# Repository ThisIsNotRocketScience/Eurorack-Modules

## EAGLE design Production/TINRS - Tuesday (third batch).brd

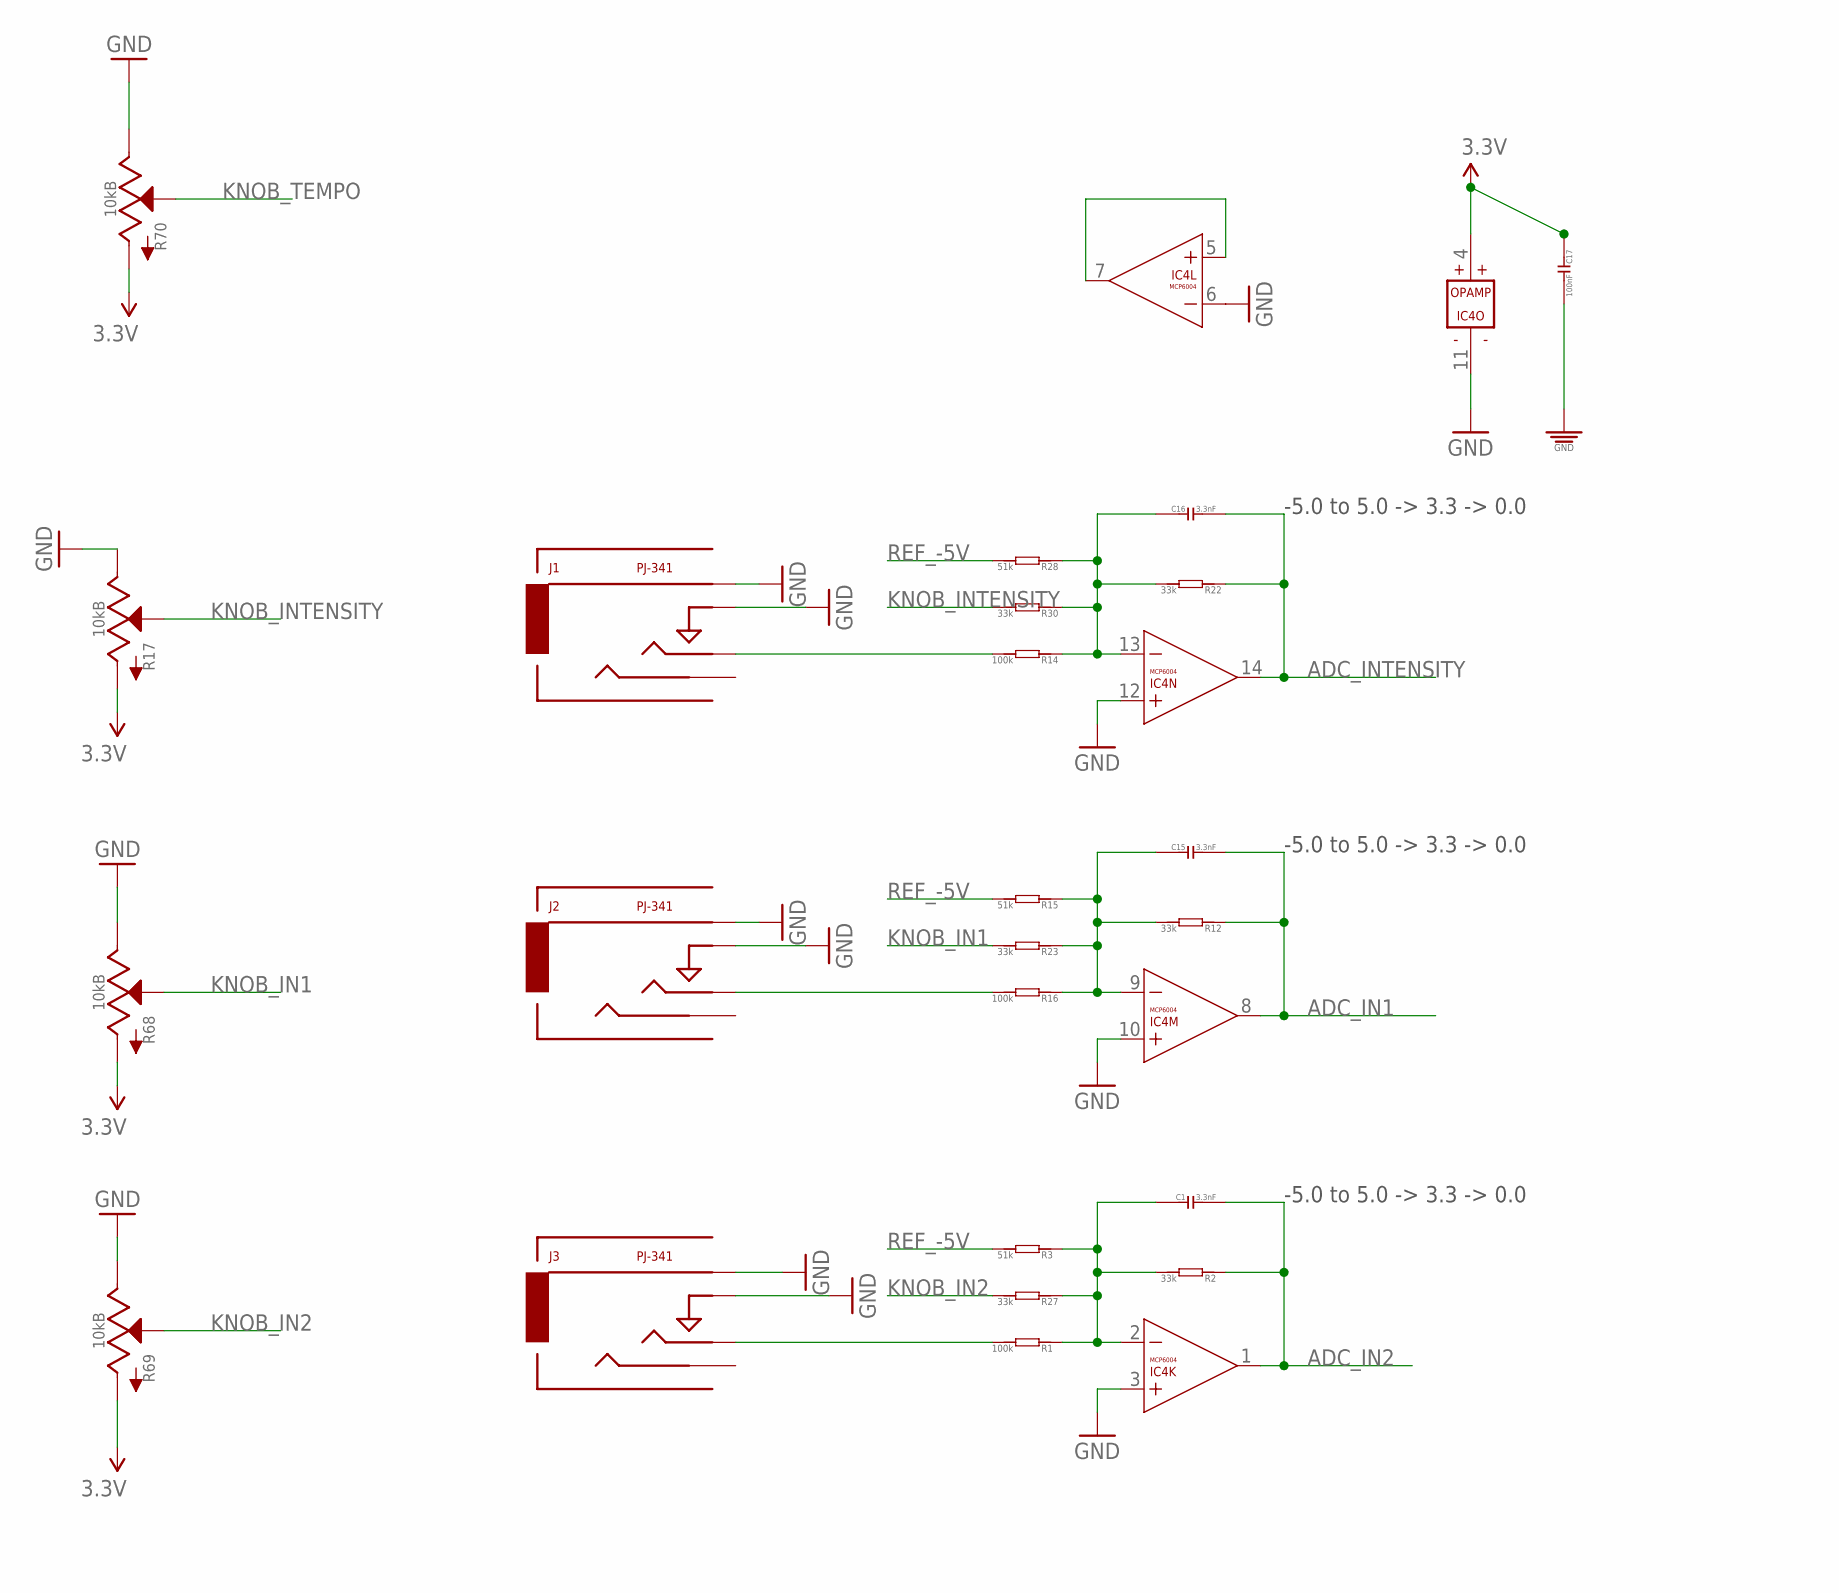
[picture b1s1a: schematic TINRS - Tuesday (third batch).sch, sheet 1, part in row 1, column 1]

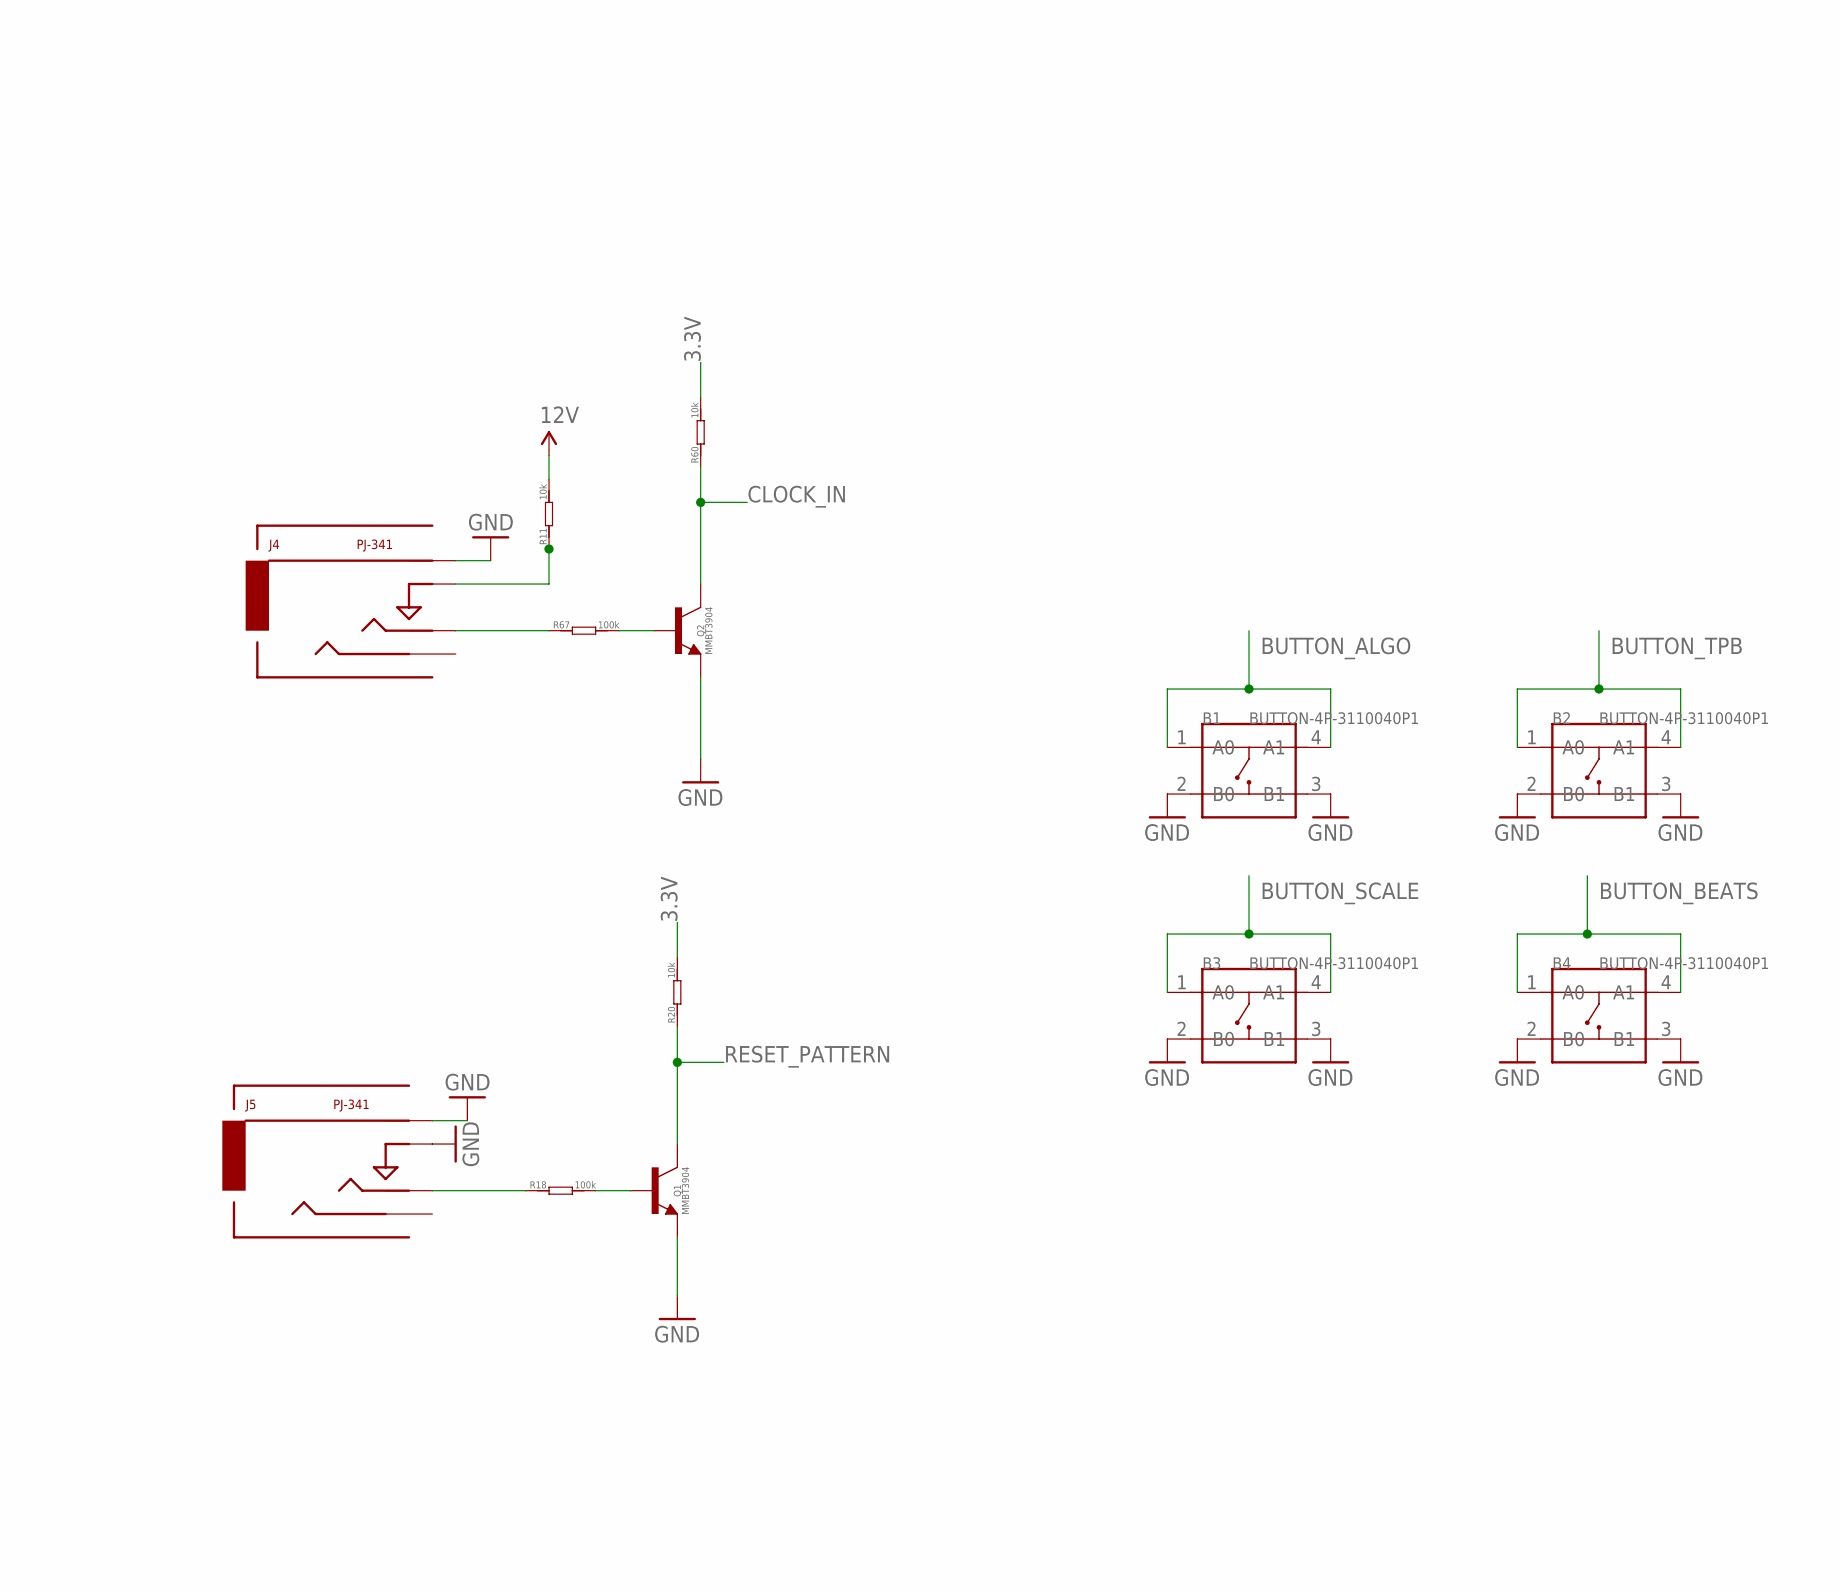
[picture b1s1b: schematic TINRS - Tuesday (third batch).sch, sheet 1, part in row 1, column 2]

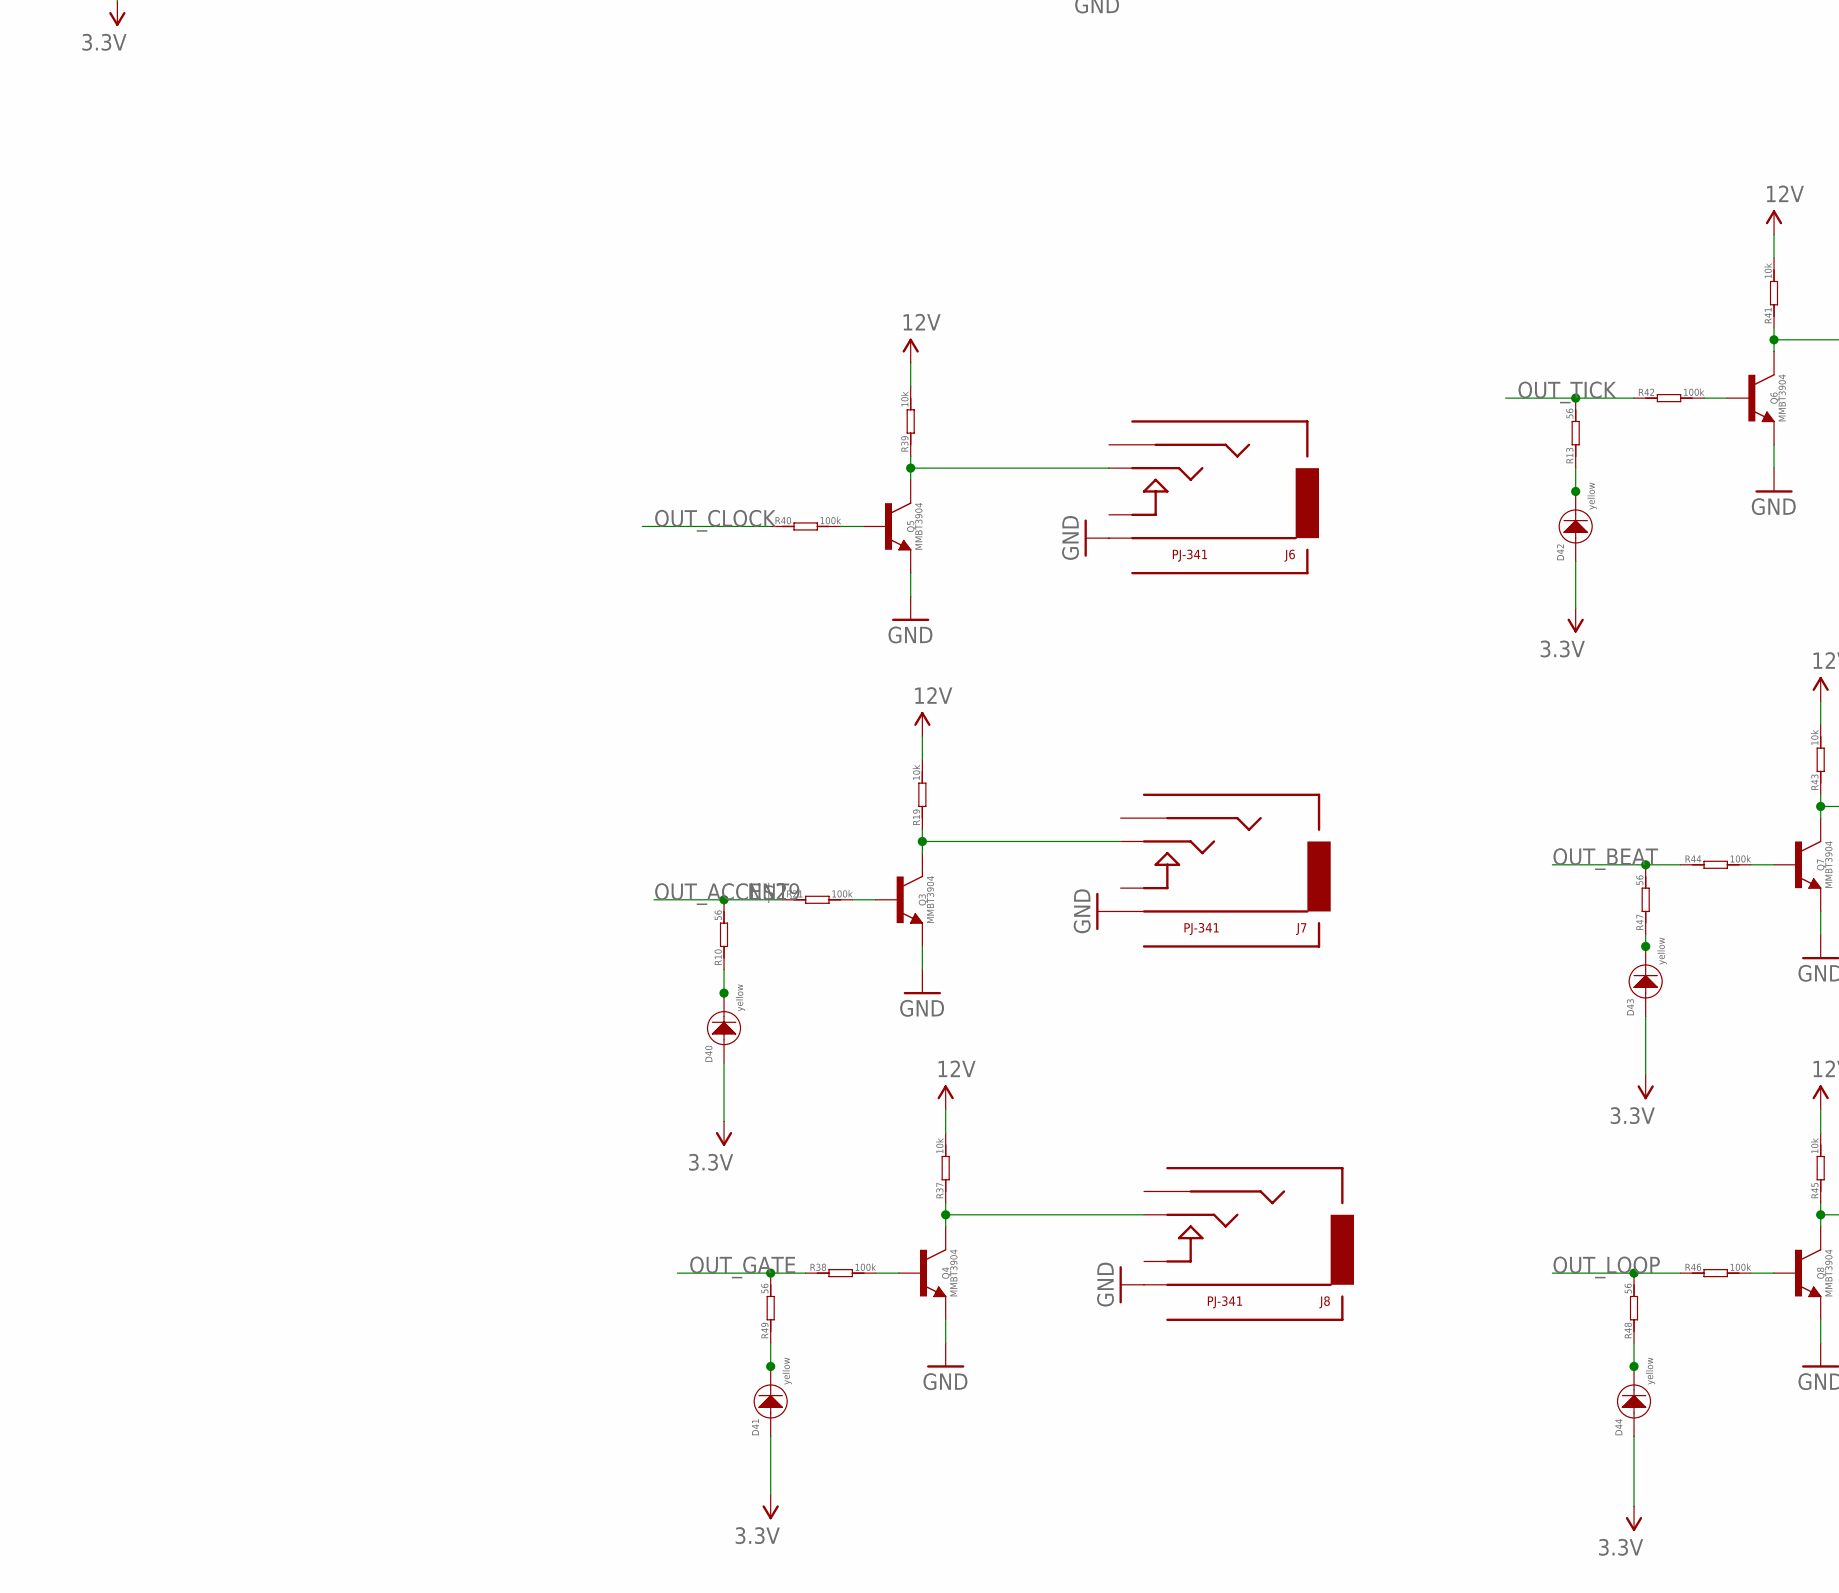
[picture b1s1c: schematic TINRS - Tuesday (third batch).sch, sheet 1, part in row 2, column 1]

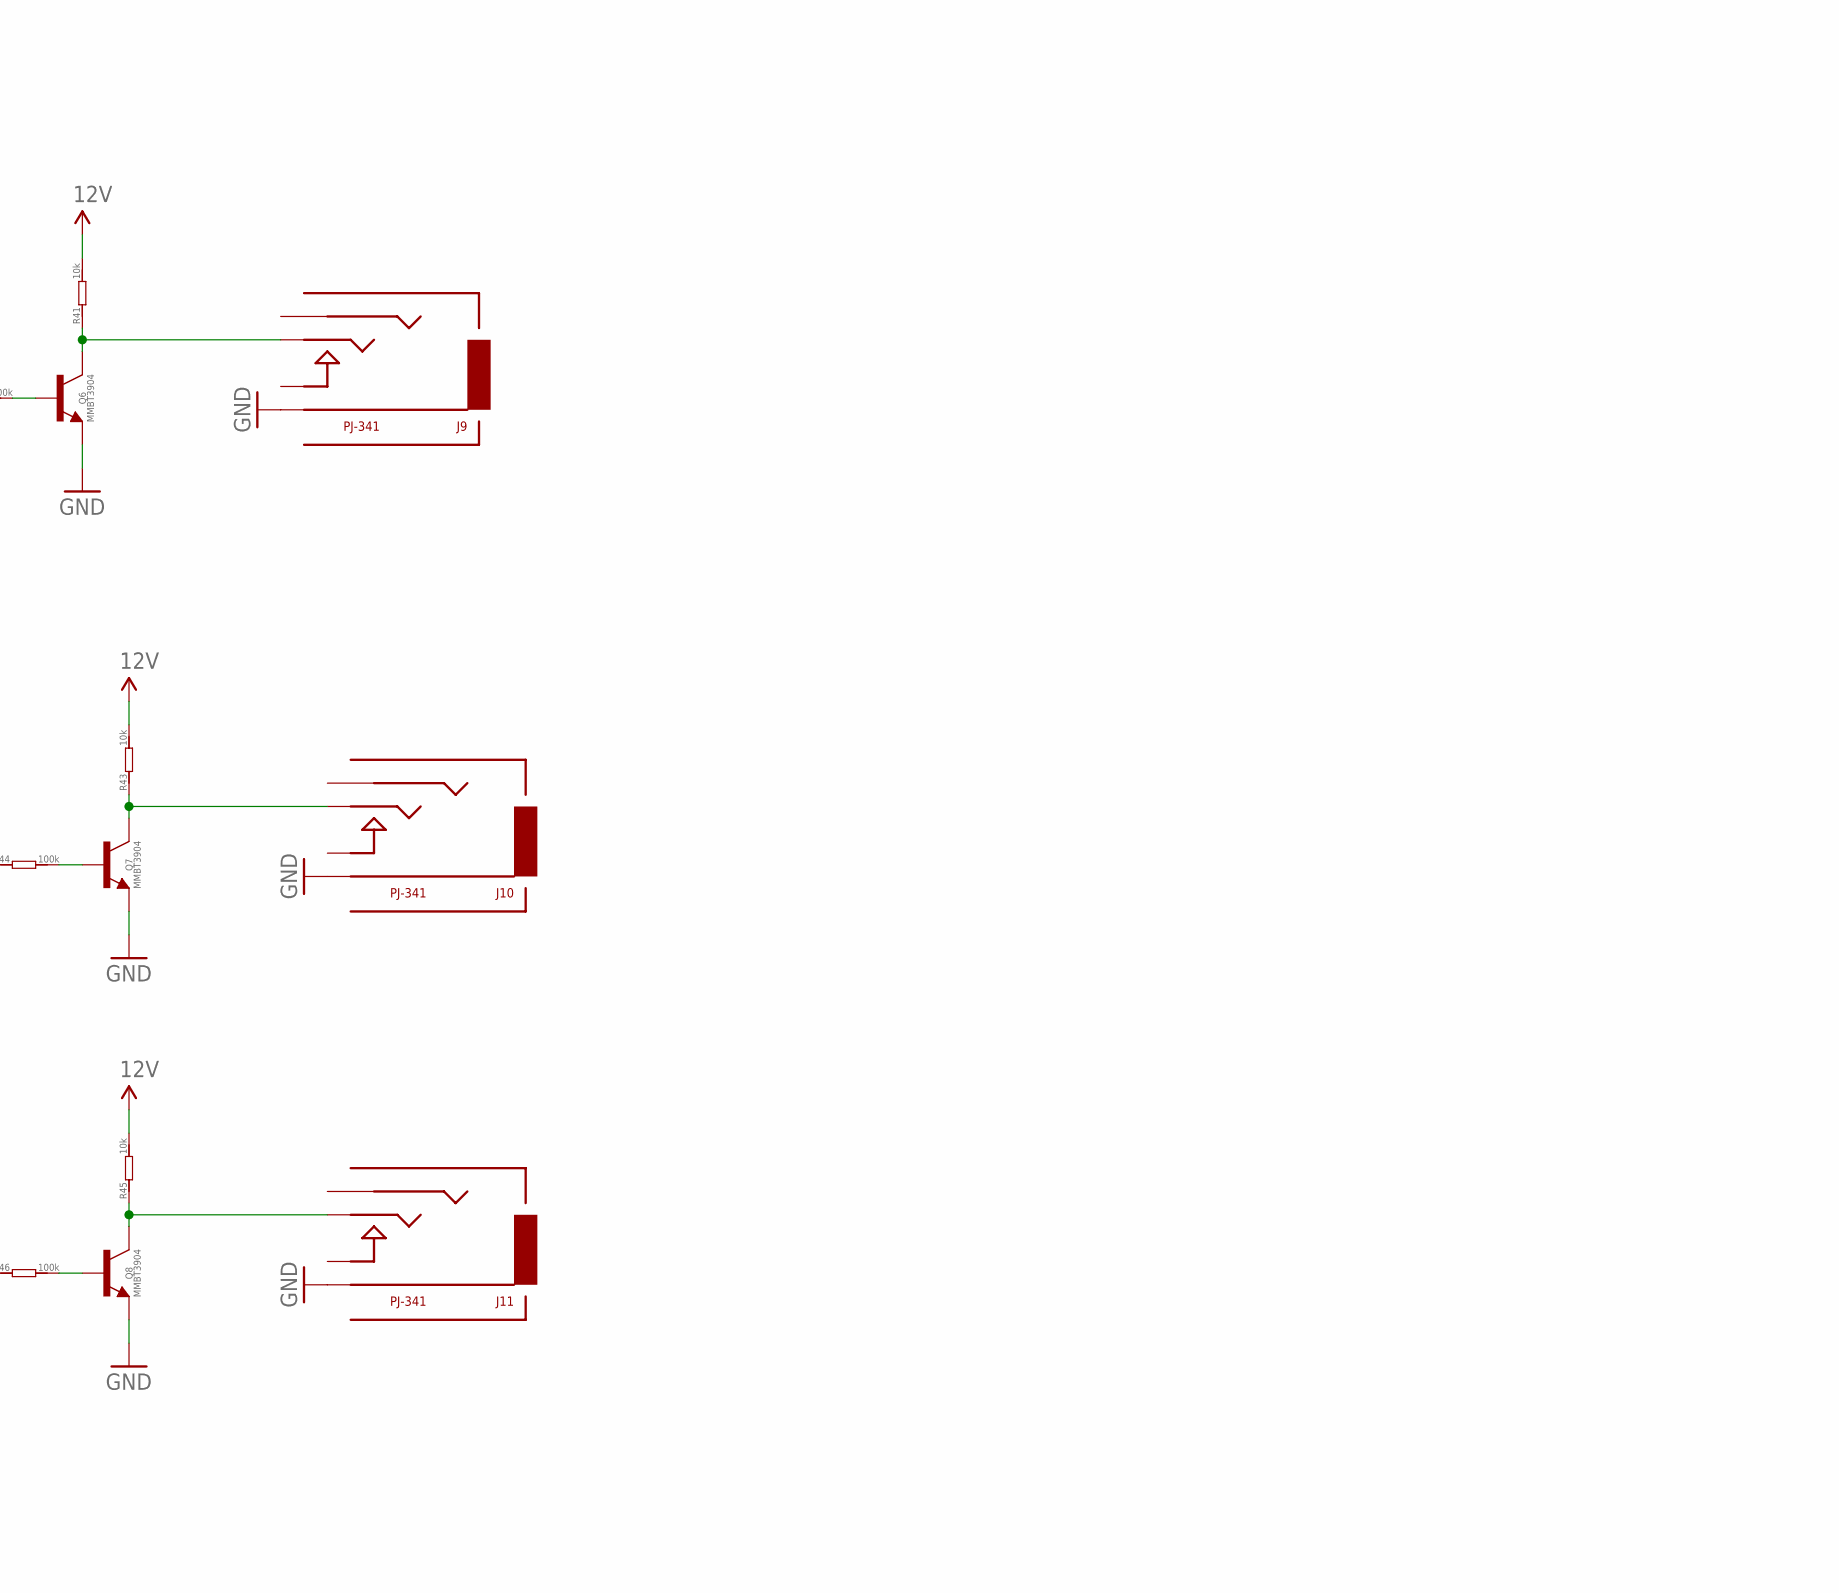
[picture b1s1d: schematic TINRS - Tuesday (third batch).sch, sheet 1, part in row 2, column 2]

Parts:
B1, B2, B3, B4: BUTTON-4P-3110040P1; 4P-6.0X6.0X5.0H
C1, C15, C16: 3.3nF; C0603
C17: 100nF; C0603; MPN MC0603F104Z160CT
D40, D41, D42, D43, D44: yellow; 3MMLED
IC4: MCP6004; SO14; MPN MCP6004-I/SL.
J1, J2, J3, J4, J5: PJ-341; 3.5MM-JACK-SWITCH-13MM-INPUT
J6, J7, J8, J9, J10, J11: PJ-341; 3.5MM-JACK-SWITCH-13MM-OUTPUT
Q1, Q2, Q3, Q4, Q5, Q6, Q7, Q8: MMBT3904; SOT23-BEC; MPN PMBT3904,215
R1, R14, R16, R18, R21, R38, R40, R42, R44, R46, R67: 100k; R0603
R2, R12, R22, R23, R27, R30: 33k; R0603
R3, R15, R28: 51k; R0603
R10, R13, R47, R48, R49: 56; R0603
R11, R19, R20, R37, R39, R41, R43, R45, R60: 10k; R0603
R17, R68, R69, R70: 10kB; ALPS_POT_SQUAREHOLES

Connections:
3.3V: C17.1, D40.+, D41.+, D42.+, D43.+, D44.+, IC4.4 (V+), R17.P$3 (A), R20.2, R60.2, R68.P$3 (A), R69.P$3 (A), R70.P$3 (A); also elsewhere on the board
12V: R11.2, R19.2, R37.2, R39.2, R41.2, R43.2, R45.2; also elsewhere on the board
ADC_IN1: C15.2, IC4.8 (OUT), R12.1; also elsewhere on the board
ADC_IN2: C1.2, IC4.1 (OUT), R2.1; also elsewhere on the board
ADC_INTENSITY: C16.2, IC4.14 (OUT), R22.1; also elsewhere on the board
BUTTON_ALGO: B1.1 (A0), B1.4 (A1); also elsewhere on the board
BUTTON_BEATS: B4.1 (A0), B4.4 (A1); also elsewhere on the board
BUTTON_SCALE: B3.1 (A0), B3.4 (A1); also elsewhere on the board
BUTTON_TPB: B2.1 (A0), B2.4 (A1); also elsewhere on the board
CLOCK_IN: Q2.C, R60.1; also elsewhere on the board
D21: D43.-, R47.1
GND: B1.2 (B0), B1.3 (B1), B2.2 (B0), B2.3 (B1), B3.2 (B0), B3.3 (B1), B4.2 (B0), B4.3 (B1), C17.2, IC4.3 (+IN), IC4.6 (-IN), IC4.10 (+IN), IC4.11 (V-), IC4.12 (+IN), J1.RING@3 (RING), J1.SWITCH@3 (SWITCH), J2.RING@3 (RING), J2.SWITCH@3 (SWITCH), J3.RING@3 (RING), J3.SWITCH@3 (SWITCH), J4.RING@3 (RING), J5.RING@3 (RING), J5.SWITCH@3 (SWITCH), J6.RING@3 (RING), J7.RING@3 (RING), J8.RING@3 (RING), J9.RING@3 (RING), J10.RING@3 (RING), J11.RING@3 (RING), Q1.E, Q2.E, Q3.E, Q4.E, Q5.E, Q6.E, Q7.E, Q8.E, R17.P$1 (E), R68.P$1 (E), R69.P$1 (E), R70.P$1 (E); also elsewhere on the board
KNOB_IN1: R23.2, R68.P$2 (S)
KNOB_IN2: R27.2, R69.P$2 (S)
KNOB_INTENSITY: R17.P$2 (S), R30.2
KNOB_TEMPO: R70.P$2 (S); also elsewhere on the board
unnamed: J2.TIP@3 (TIP), R16.2
unnamed: C15.1, IC4.9 (-IN), R12.2, R15.1, R16.1, R23.1
unnamed: J3.TIP@3 (TIP), R1.2
unnamed: C1.1, IC4.2 (-IN), R1.1, R2.2, R3.1, R27.1
unnamed: D42.-, R13.1
unnamed: Q1.B, R18.2
unnamed: J5.TIP@3 (TIP), R18.1
unnamed: D40.-, R10.1
unnamed: Q3.B, R21.2
unnamed: J7.TIP@3 (TIP), Q3.C, R19.1
unnamed: J1.TIP@3 (TIP), R14.2
unnamed: C16.1, IC4.13 (-IN), R14.1, R22.2, R28.1, R30.1
unnamed: J4.TIP@3 (TIP), R67.1
unnamed: D41.-, R49.1
unnamed: D44.-, R48.1
unnamed: Q4.B, R38.2
unnamed: J8.TIP@3 (TIP), Q4.C, R37.1
unnamed: Q5.B, R40.2
unnamed: J6.TIP@3 (TIP), Q5.C, R39.1
unnamed: Q6.B, R42.2
unnamed: J9.TIP@3 (TIP), Q6.C, R41.1
unnamed: Q2.B, R67.2
unnamed: Q7.B, R44.2
unnamed: J10.TIP@3 (TIP), Q7.C, R43.1
unnamed: Q8.B, R46.2
unnamed: J11.TIP@3 (TIP), Q8.C, R45.1
unnamed: J4.SWITCH@3 (SWITCH), R11.1
unnamed: IC4.5 (+IN), IC4.7 (OUT)
OUT_ACCENT: R10.2, R21.1; also elsewhere on the board
OUT_BEAT: R44.1, R47.2; also elsewhere on the board
OUT_CLOCK: R40.1; also elsewhere on the board
OUT_GATE: R38.1, R49.2; also elsewhere on the board
OUT_LOOP: R46.1, R48.2; also elsewhere on the board
OUT_TICK: R13.2, R42.1; also elsewhere on the board
REF_-5V: R3.2, R15.2, R28.2; also elsewhere on the board
RESET_PATTERN: Q1.C, R20.1; also elsewhere on the board

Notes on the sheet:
-5.0 to 5.0 -> 3.3 -> 0.0

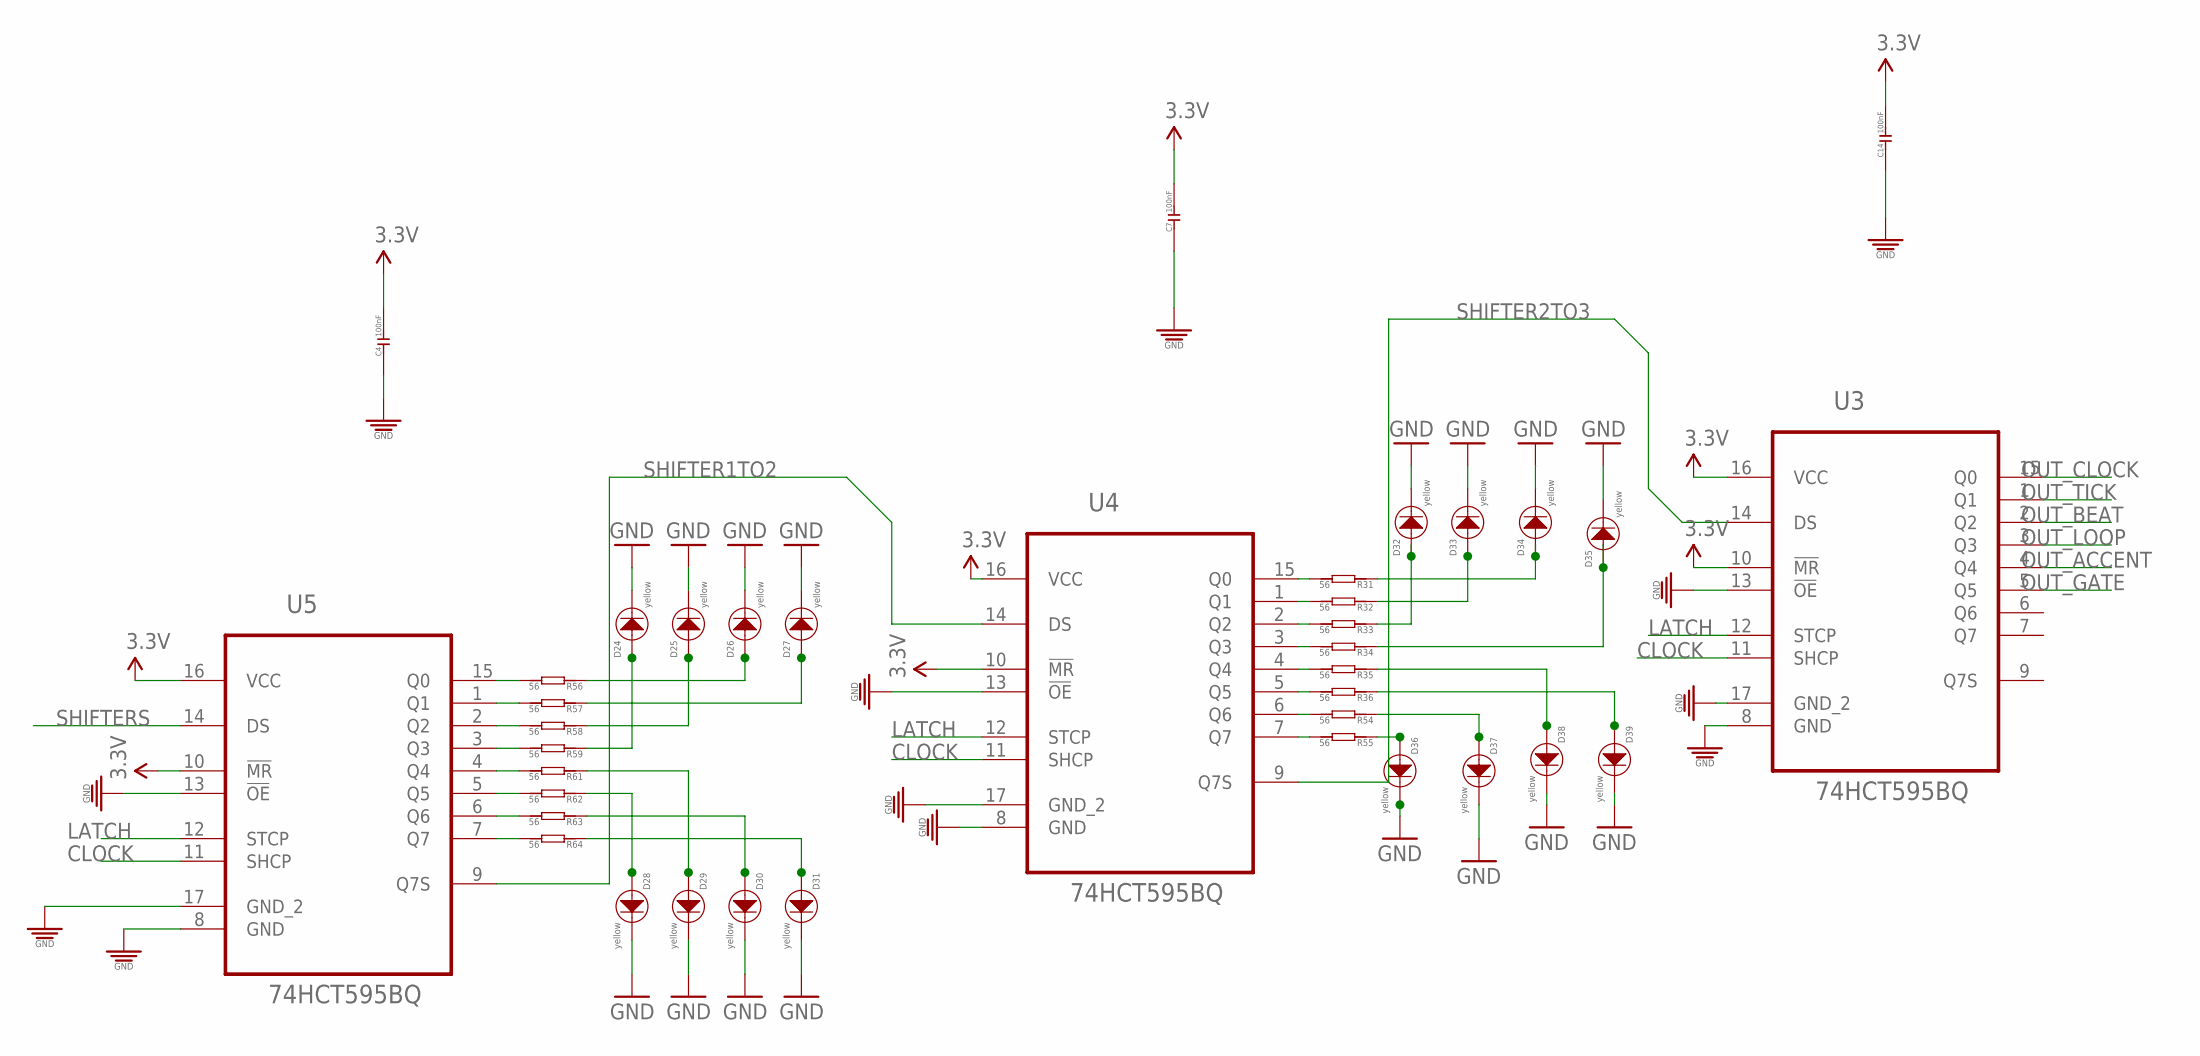
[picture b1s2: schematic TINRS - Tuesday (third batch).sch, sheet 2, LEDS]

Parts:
C4, C7, C14: 100nF; C0603; MPN MC0603F104Z160CT
D24, D25, D26, D27, D28, D29, D30, D31, D32, D33, D34, D35, D36, D37, D38, D39: yellow; 3MMLED
R31, R32, R33, R34, R35, R36, R54, R55, R56, R57, R58, R59, R61, R62, R63, R64: 56; R0603
U3, U4, U5: 74HCT595BQ; QFN50P250X350X100-17N

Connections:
3.3V: C4.2, C7.2, C14.2, U3.10 (!MR), U3.16 (VCC), U4.10 (!MR), U4.16 (VCC), U5.10 (!MR), U5.16 (VCC); also elsewhere on the board
CLOCK: U3.11 (SHCP), U4.11 (SHCP), U5.11 (SHCP); also elsewhere on the board
GND: C4.1, C7.1, C14.1, D24.-, D25.-, D26.-, D27.-, D28.-, D29.-, D30.-, D31.-, D32.-, D33.-, D34.-, D35.-, D36.-, D37.-, D38.-, D39.-, U3.8 (GND), U3.13 (!OE), U3.17 (GND_2), U4.8 (GND), U4.13 (!OE), U4.17 (GND_2), U5.8 (GND), U5.13 (!OE), U5.17 (GND_2); also elsewhere on the board
LATCH: U3.12 (STCP), U4.12 (STCP), U5.12 (STCP); also elsewhere on the board
unnamed: R32.2, U4.1 (Q1)
unnamed: R33.2, U4.2 (Q2)
unnamed: R34.2, U4.3 (Q3)
unnamed: R35.2, U4.4 (Q4)
unnamed: D28.+, R62.1
unnamed: R36.2, U4.5 (Q5)
unnamed: R54.2, U4.6 (Q6)
unnamed: D29.+, R61.1
unnamed: R55.2, U4.7 (Q7)
unnamed: R31.2, U4.15 (Q0)
unnamed: R56.2, U5.15 (Q0)
unnamed: R57.2, U5.1 (Q1)
unnamed: R58.2, U5.2 (Q2)
unnamed: R59.2, U5.3 (Q3)
unnamed: R61.2, U5.4 (Q4)
unnamed: R62.2, U5.5 (Q5)
unnamed: R63.2, U5.6 (Q6)
unnamed: R64.2, U5.7 (Q7)
unnamed: D27.+, R57.1
unnamed: D26.+, R56.1
unnamed: D25.+, R58.1
unnamed: D24.+, R59.1
unnamed: D30.+, R63.1
unnamed: D31.+, R64.1
unnamed: D32.+, R33.1
unnamed: D33.+, R32.1
unnamed: D34.+, R31.1
unnamed: D35.+, R34.1
unnamed: D36.+, R55.1
unnamed: D37.+, R54.1
unnamed: D38.+, R35.1
unnamed: D39.+, R36.1
OUT_ACCENT: U3.4 (Q4); also elsewhere on the board
OUT_BEAT: U3.2 (Q2); also elsewhere on the board
OUT_CLOCK: U3.15 (Q0); also elsewhere on the board
OUT_GATE: U3.5 (Q5); also elsewhere on the board
OUT_LOOP: U3.3 (Q3); also elsewhere on the board
OUT_TICK: U3.1 (Q1); also elsewhere on the board
SHIFTER1TO2: U4.14 (DS), U5.9 (Q7S)
SHIFTER2TO3: U3.14 (DS), U4.9 (Q7S)
SHIFTERS: U5.14 (DS); also elsewhere on the board

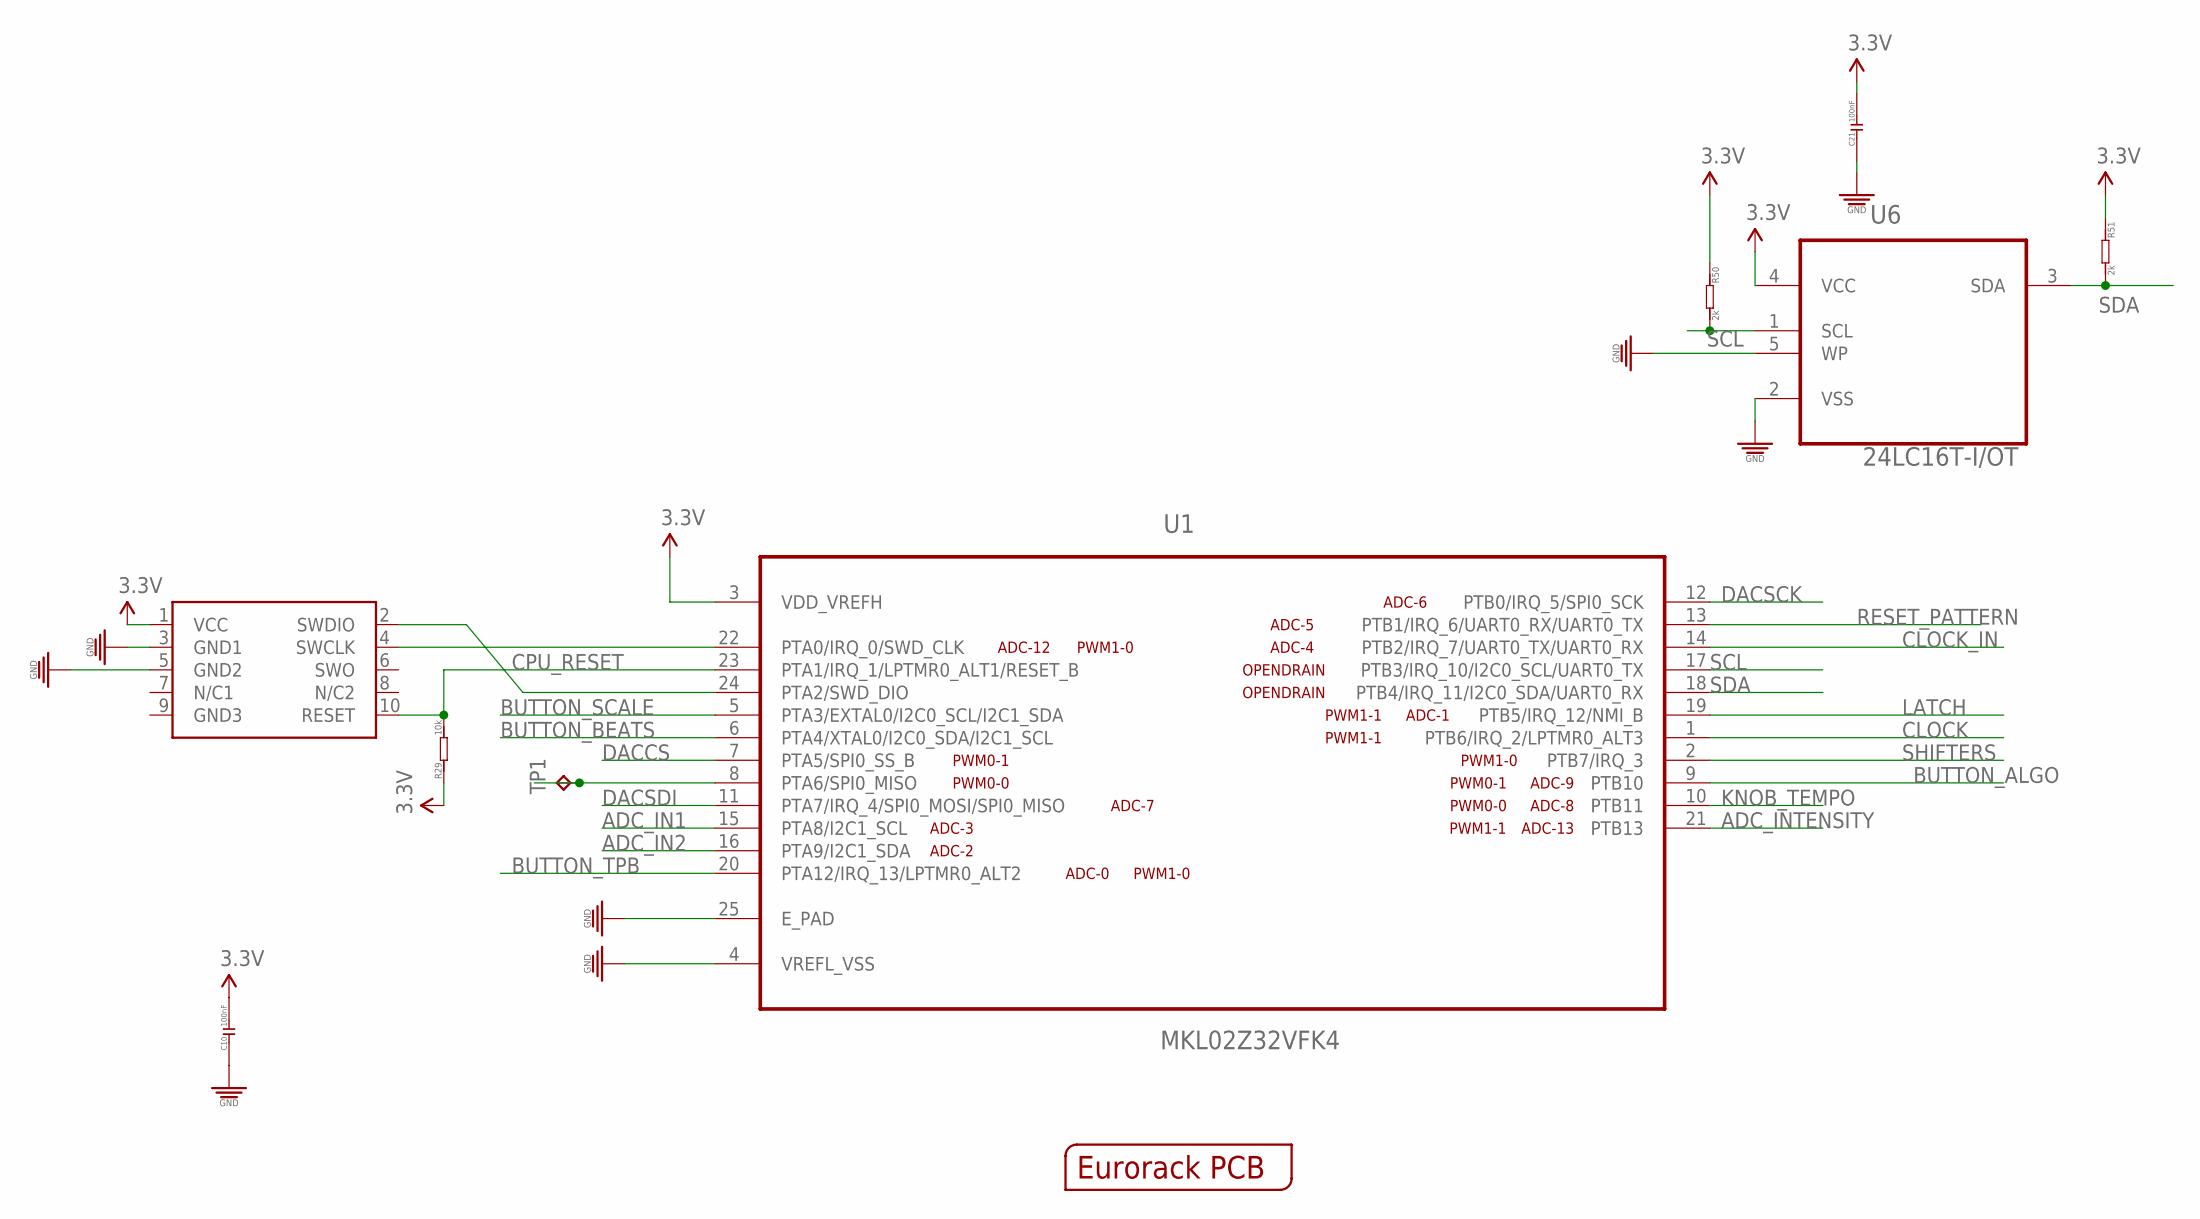
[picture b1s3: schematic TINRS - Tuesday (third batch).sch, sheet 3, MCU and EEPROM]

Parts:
C10, C21: 100nF; C0603; MPN MC0603F104Z160CT
OUTLINE: EURORACK_PCB12HP; EURORACK12HPPCB
R29: 10k; R0603
R50, R51: 2k; R0603
SWD1: CORTEX_SWD; M50-3600542
TP1: TPB1,27; B1,27
U1: MKL02Z32VFK4; QFN50P400X400X100-25N
U6: 24LC16T-I/OT; SOT95P290X145-5N; MPN 24LC00T-I/OT

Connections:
3.3V: C10.2, C21.2, R29.1, R50.1, R51.1, SWD1.1 (VCC), U1.3 (VDD_VREFH), U6.4 (VCC); also elsewhere on the board
ADC_IN1: U1.15 (PTA8/I2C1_SCL); also elsewhere on the board
ADC_IN2: U1.16 (PTA9/I2C1_SDA); also elsewhere on the board
ADC_INTENSITY: U1.21 (PTB13); also elsewhere on the board
BUTTON_ALGO: U1.9 (PTB10); also elsewhere on the board
BUTTON_BEATS: U1.6 (PTA4/XTAL0/I2C0_SDA/I2C1_SCL); also elsewhere on the board
BUTTON_SCALE: U1.5 (PTA3/EXTAL0/I2C0_SCL/I2C1_SDA); also elsewhere on the board
BUTTON_TPB: U1.20 (PTA12/IRQ_13/LPTMR0_ALT2); also elsewhere on the board
CLOCK: U1.1 (PTB6/IRQ_2/LPTMR0_ALT3); also elsewhere on the board
CLOCK_IN: U1.14 (PTB2/IRQ_7/UART0_TX/UART0_RX); also elsewhere on the board
CPU_RESET: R29.2, SWD1.10 (RESET), U1.23 (PTA1/IRQ_1/LPTMR0_ALT1/RESET_B)
DACCS: U1.7 (PTA5/SPI0_SS_B); also elsewhere on the board
DACSCK: U1.12 (PTB0/IRQ_5/SPI0_SCK); also elsewhere on the board
DACSDI: U1.11 (PTA7/IRQ_4/SPI0_MOSI/SPI0_MISO); also elsewhere on the board
GND: C10.1, C21.1, SWD1.3 (GND1), SWD1.5 (GND2), U1.4 (VREFL_VSS), U1.25 (E_PAD), U6.2 (VSS), U6.5 (WP); also elsewhere on the board
KNOB_TEMPO: U1.10 (PTB11); also elsewhere on the board
LATCH: U1.19 (PTB5/IRQ_12/NMI_B); also elsewhere on the board
PTA6: TP1.TP, U1.8 (PTA6/SPI0_MISO)
RESET_PATTERN: U1.13 (PTB1/IRQ_6/UART0_RX/UART0_TX); also elsewhere on the board
SCL: R50.2, U1.17 (PTB3/IRQ_10/I2C0_SCL/UART0_TX), U6.1 (SCL)
SDA: R51.2, U1.18 (PTB4/IRQ_11/I2C0_SDA/UART0_RX), U6.3 (SDA)
SHIFTERS: U1.2 (PTB7/IRQ_3); also elsewhere on the board
SWD_CLK: SWD1.4 (SWCLK), U1.22 (PTA0/IRQ_0/SWD_CLK)
SWD_DIO: SWD1.2 (SWDIO), U1.24 (PTA2/SWD_DIO)

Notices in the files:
parts and their libraries:
SparkFun-Aesthetics: Licensing: CC v3.0 Share-Alike You are welcome to use this library for commercial purposes.
